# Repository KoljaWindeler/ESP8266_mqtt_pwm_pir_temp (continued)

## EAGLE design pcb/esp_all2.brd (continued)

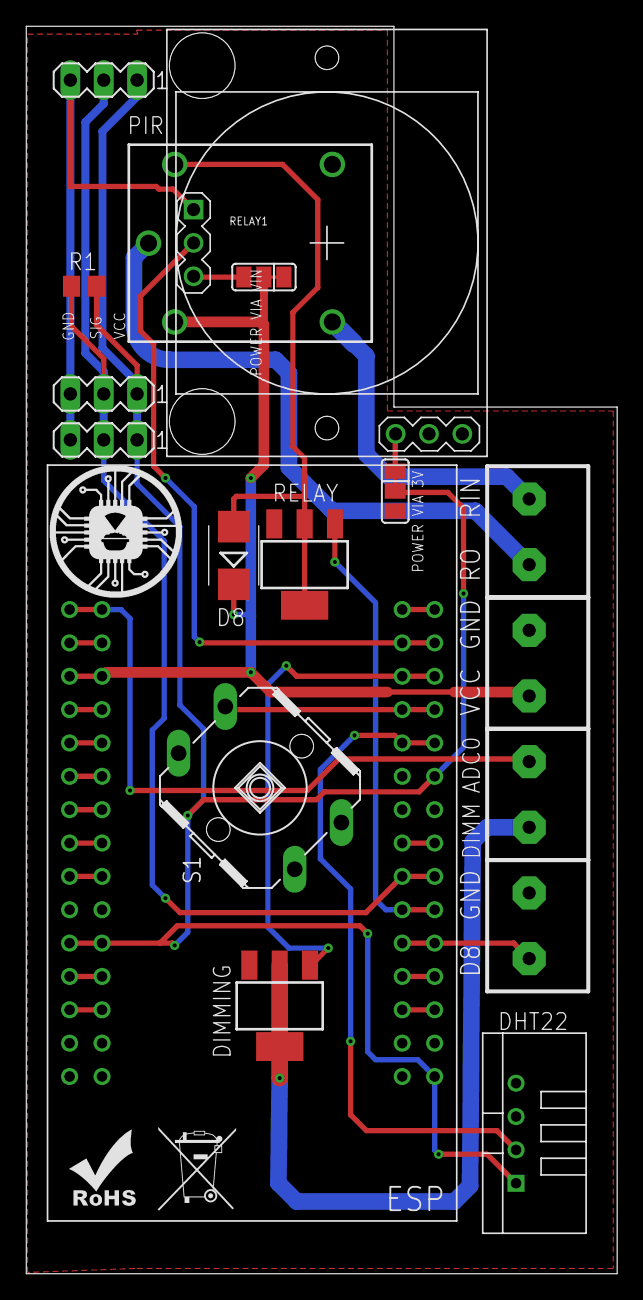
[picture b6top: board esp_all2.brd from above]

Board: 2 copper layers, 45.0 x 95.0 mm, 22 parts (1 on the bottom side), 30 nets.

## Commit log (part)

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2018-04-24 added current release
2018-06-18 Add "button relased after N"
2018-06-18 Added button release topic
2018-06-24 Fix: Missing Return if no update is required
2018-06-24 Fix: Missing return statement if no update required
2018-06-27 on for feature added
2018-07-11 backup 20180611
2018-07-16 added push bullet info
2018-07-23 updated sprinkler
2018-07-24 added Caro to PB
2018-09-02 added comments
2018-09-08 Added audio streaming via i2c (UART0RX). Decoding has to be done on pc. Mp3 decoding wouldn't fit into flash (tested)
2018-09-10 -renamed all files to "cap_" if they are pure capabilities - added freq counter
2018-09-17 Add universal pin to the simple light to support shelly
2018-09-17 add option to use other pins
2018-09-17 added wider parsing header
2018-09-17 Move to a more general button pin approach
2018-09-17 added pin as member var
2018-09-17 Moved bridge and husqvarna to no compile to save some Flash
2018-09-17 use parse_wide function
2018-09-17 moved strings to flash
2018-09-23 Initial version with SigmaDelta
2018-09-23 clean up
2018-09-23 incread oversampling
2018-09-27 i2s working fine, but popping
2018-09-27 44.1kHz @ 16Bit stable
2018-09-27 acceppt stuttering
2018-09-27 Audio bitrate selectable, AUD16 for 16 bit, AUD1 (NOT AUD8) for 8bit
2018-09-27 version update
2018-09-28 removed debug output
2018-10-03 moved audio to play
2018-10-03 moved tcp based audio to udp based play
2018-10-03 added untested recorder capability
2018-10-03 clean up, bug hunting
2018-10-03 fixed buggy config writing over limits due to non-rewind pointer
2018-10-04 universal read write function for eepro
2018-10-04 detache interrupt only if it was attached previously
2018-10-04 added some improvements for shelly
2018-10-04 upd stream without tcp disconnect, untested
2018-10-04 added milling board
2018-10-04 release
2018-10-04 detach interrupt on destructor
2018-10-04 added RAM output after obj init
2018-10-04 Switch back to TCP, udP simply not stable
2018-10-04 increased timeout
2018-10-07 move to nuc
2018-10-15 significan click reduction
2018-10-15 added sample rate selection
2018-10-15 added reconnect
2018-10-16 timeout avoid message support, soundless
2018-10-22 updates times
2018-10-22 removed option for non-interrupt mode, get ridge of pulseIn
2018-10-22 added compile options, removed default funcitons from all clases
2018-10-22 reworked general dependency stucture to general approache
2018-10-22 renamed mesh -> it is a capability
2018-10-22 added useless files
2018-10-22 added default notes to template
2018-10-22 renamed misleading classes and files
2018-11-08 added pins in arduino way
2018-11-08 non working version,
2018-11-12 added libs
2018-11-14 added scrpts
2018-11-24 added workbench appdeamon
2018-11-27 pi added
2018-12-09 updated scripts
2018-12-18 Updated appdaemon scripts
2018-12-18 set yaml as lovelace method
2018-12-19 BONE: changed key GPIO: fixed input pullup Button: Updated for versatile Button options
2018-12-27 added presents simulation:
2019-01-09 uodated global motion
2019-03-16 20190316
2019-03-18 fixed ce muell
2019-04-22 backup 20190422
2019-04-22 updated custom sensor according to update info
2019-04-22 removed client id from mqtt logon
2019-04-26 added manifest for 0.i2
2019-05-01 added connection checker
2019-05-04 weather
2019-05-24 20190524 backup
2019-06-18 20190618
2019-06-18 update timing of ding dong
    use HA command to take a snapshot
2019-06-18 inital version of domecam
2019-06-20 Update Readme.md
    Update documentation, have to check src file
2019-06-20 Update xiaomi_vac.yaml
    change default position of cleaning to on
2019-06-20 add second vac
2019-06-20 remove drivetime
2019-06-20 remove known devs
2019-06-20 add domecam
2019-06-20 change to onvif
2019-06-20 renamed disabled packages
2019-06-20 disable play, not used anyway
2019-06-20 typo fix
2019-06-20 added UTP99 as uptimer of millis (minutes based on millis)
2019-06-20 pullup only for negative connecting pushbutton
2019-06-21 Update xiaomi_vac.yaml
    removed automation, this is migrated to app deamon
2019-06-21 Update xiaomi_vac.py
    added second vac and rewrote script with variable entity amounts
2019-06-21 Update xiaomi_vac.yaml
    added second cleaning done switch
2019-06-21 Update ui-lovelace.yaml
    added second cleaning_done switch
2019-06-21 updated cameras
2019-06-21 added two switches, one per vac
2019-06-22 Version update, release 20190622
2019-06-22 fix counter
2019-06-22 backup 20190622
2019-06-25 added some SONOFF 4ch infos
2019-06-25 minor formating
2019-06-26 Update Readme.md
    Nightlight topic is "night", not "nightlight".
2019-06-26 updated internal function to work with new esp core
2019-06-26 added missing return statements
2019-06-26 added random pin to ds sensor
2019-06-26 Correction of Readme, some config changed..
2019-06-26 added support for random PIR pin
2019-06-26 new release with random pin assignment for most capability
2019-06-26 char limit
2019-06-26 Add config example
2019-06-26 change so the rule will only trigger once
2019-06-26 Set state on trigger off
2019-06-26 change icon of security state
2019-06-26 added light to kitchen group
2019-06-26 added kitchen light
2019-06-26 Add dev5
2019-06-26 added safe storage files
2019-06-27 added ICACHE_RAM_ATTR attributes for ISR routines
2019-06-27 minor warning fix2
2019-07-01 added discovery support
2019-07-01 moved connected time to global scope
2019-07-01 added unsubscribe support
2019-07-01 rearranged receive and send in loop
2019-07-02 Simplify discovery
    remove check if config is the same and send it regardless. this make so code much smaller and shouldn't hurt (to be tested)
2019-07-03 adding optional discovery support
2019-07-04 Added 1sec support
2019-07-04 Added discovery option to ADC
2019-07-04 added discovery
2019-07-04 enabled publish for discovery
2019-07-04 added bool m_discovery_pub;
2019-07-04 Added basic GPIO discovery
2019-07-04 Move 7am control to appdeamon
2019-07-04 backup config 20190704
2019-07-04 updated template
2019-07-04 added release 20190704 with basic discovery feature
2019-07-05 added custom component and discovery info
2019-07-05 Create LICENSE
2019-07-05 added retain flag
2019-07-06 modified button1s payload to ON/OFF
2019-07-06 moved files towards discovery template
2019-07-07 Backup 20190707
2019-07-08 moved towards template
2019-07-08 moved to template
2019-07-08 Template
2019-07-08 added discovery info
2019-07-08 added basic discovery for dimming, single channel
2019-07-08 added discovery for dimm to B1,AI and PWM
2019-07-09 backup 20190709
2019-07-10 added "you've left the lights on" script
2019-07-10 backup 20190710
2019-07-14 added support for discovery with complex device Id
2019-07-15 fixed bug in discovery name has a hierarchy
2019-07-24 added basic energy meter parsing
2019-08-12 backup 20190812
2019-08-12 added new release, including IR capability
2019-09-03 added discovery to DHT sensor
2019-09-03 backup 20190903
2019-09-13 Update cap_button.cpp
    added option "GHOST" to enable ghost switching avoidance
2019-09-13 added option "GHOST" to enable ghost switching avoidance m_ghost_avoidance
2019-09-13 added GHOST feature with timing, e.g. GHOST80 for 80ms
2019-09-20 added rfb .. some makeup is still needed
2019-09-27 backup 20190927
2019-10-08 added more option to overcome owntracks reporings in the morning
2019-10-16 added async processing of button
2019-10-16 added async button processing
2019-10-16 moved button code from interrupt
2019-10-21 added button callback
2019-10-21 added wifi button callback option
2019-10-21 changed callback'
2019-10-21 tested and release of async button handling without interrupt
2019-10-23 fixed ghostavoidance with state prediction
2019-10-29 backup 20191029
2019-10-29 backup 20191029_2
2019-11-03 Added Serial Server capability
2019-11-04 add m_no_BL_conn
2019-11-04 added NOBLCONN and increased button push to setup count to 20
2019-11-24 backup 20191124
2019-11-27 added option to dimm and set linear instead of half log
2019-11-27 added option to dimm linear instead of half log
    GOP / GON are regular GPIO_OUTPUT_POSITIV and GPIO_OUTPUT_NEGATIV but
    GOLP / GOLN are GPIO_OUTPUT_LINEAR_POSITIV and GPIO_OUTPUT_LINEAR_NEGATIV .. L is not really easy as it could be LINEAR or LOG .. but thats life
2019-11-27 Update readme, added Linear GPIO mode
2019-11-27 fixed pointer bug
2019-11-30 moved serser from softserial to hardserial
2019-12-04 Create long term battery observation
2019-12-04 fixed of of year handling
2019-12-04 backup 20191204
2019-12-04 improved end of year fix
2019-12-08 Fixed GPIO bug
2019-12-09 updated to espressif package 2.3.1 and fixed breaking changes
2019-12-09 replaced 20191208 version with 20191209. 20191208 went over 50% PROGRAM space due to new package
2019-12-10 removed printf float support to safe memory space
2019-12-14 removed storage
2019-12-14 backup 20191214
2019-12-16 fixed long names
2020-01-02 fixed negative temperature measurements
2020-01-05 backup 20200105
2020-01-07 Update ui
2020-01-08 updated pictures
2020-01-08 backup 20200108
2020-01-12 Multiple updates, simultanious PIR handling
2020-01-12 updated readme file
2020-01-19 testing PIR delay
2020-01-21 Initial Shelly Dimmer support
2020-01-21 removed whitespaces
2020-01-22 added wattage reading for shelly dimmer
2020-01-25 backup 20200125
2020-01-28 unified light provider interface
2020-01-28 added remote simple light
2020-01-28 fixed consumption of dependency tokens
2020-01-28 bumped up version
2020-02-06 backup 20200206
2020-02-06 add manifest
2020-02-17 added discovery for L1..3
2020-02-17 always start R
2020-02-17 added boot message to count reconnect event with appdaemon
2020-02-19 initial ads support
2020-02-19 imporved ads1115 docu
2020-02-19 improved bake function
2020-02-19 added version 20200219
2020-02-26 backup 20200226
2020-03-17 added dimm speed for gpio dimming, added multi device adc
2020-03-19 ADS1115
    Adding ADS1115 pcb files
2020-03-19 improved multi device support, dedicated data rdy pin
2020-03-19 added resisitor values to schematic
2020-03-27 backup 20200327
2020-04-21 update to statemachine to avoid sleeps
2020-08-05 added freq to EM
2020-08-09 backup 20200809
2020-08-16 added fast em
2020-08-16 reset hold on release
2020-08-19 backup 20200819
2020-08-19 removed temp files
2020-10-16 backup 20201016
2020-11-13 fixed arduino core to 2.4.0, crashes with high version?
2020-11-13 fixed buffer leakage
2020-11-13 simplyfied hold reset
2020-11-13 added espsavecrash and hx711
2020-11-13 fixed em monitor old bug, reset to 1
2020-11-15 ui backup
2020-11-19 button switch will publish ON/OFF, crash limted to 1
2020-12-16 Separated HA and hardware into dedicated Respos
2021-02-22 added binary energy monitor code
2021-02-23 added filter to total values
2021-08-16 updated serser
2021-12-22 added counter module
2021-12-22 added counter to readme
2022-01-04 only consume GHOST when Button is active
2022-01-04 added release
2022-02-07 added ebus
2022-02-07 added support for multiple sensors
2022-02-07 removed serial debug
2022-02-07 hardened counter
2022-02-07 added float parameter
2022-02-07 add ebus
2023-02-04 added watch dog reset
2023-02-04 replaced by interrupt method
2023-02-04 removed neostrip, IR, serial server, added autarco
2023-02-04 added prototype for emergency
2023-02-04 removed pin high for testing
2023-02-04 added multi sensor support
2023-02-04 fixed init to value 0
2023-02-04 added new discovery methods, and watchdog handling
2023-02-04 added fireplace and autarco
2023-02-04 added watchdog handling
2023-02-04 added more datasets
2023-02-04 fixed long passwords
2023-02-04 added autarco RS485 support
2023-02-04 added fireplace, obsolete?
2023-02-08 moved old libs
2023-02-08 adding old stuff
2023-02-08 simplified discover
2023-02-08 fix spaces
2023-02-08 removed unused stuff
2023-02-08 moveing old stuff to backup
2023-04-04 changed to bake2
2023-04-04 updated version
2023-04-04 fixed new day calc
2023-11-06 added 3rd string by George
2023-11-06 added unique id for lights
2023-11-06 added release for 3rd string
2025-09-30 added new discovery method
2025-09-30 new discovery method
2025-09-30 included new discovery method
2026-04-18 added R503
2026-04-18 simplified discovery
